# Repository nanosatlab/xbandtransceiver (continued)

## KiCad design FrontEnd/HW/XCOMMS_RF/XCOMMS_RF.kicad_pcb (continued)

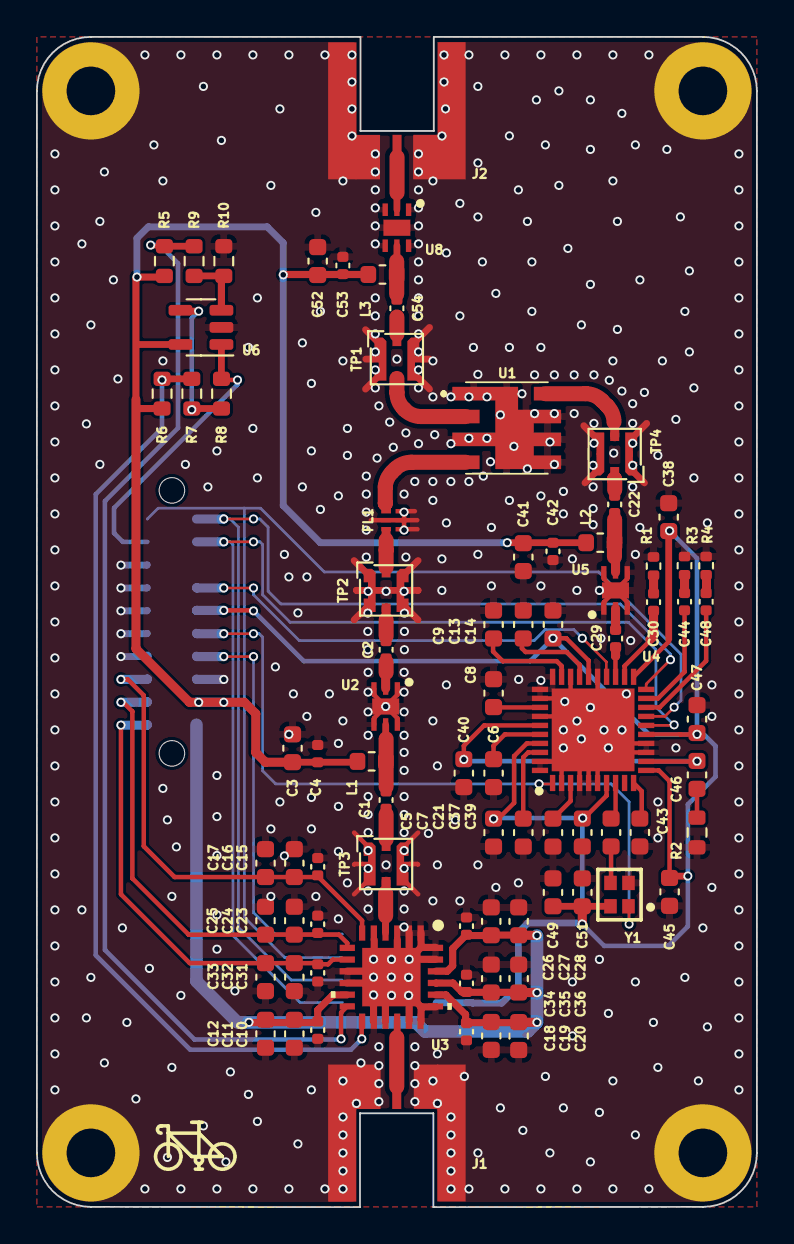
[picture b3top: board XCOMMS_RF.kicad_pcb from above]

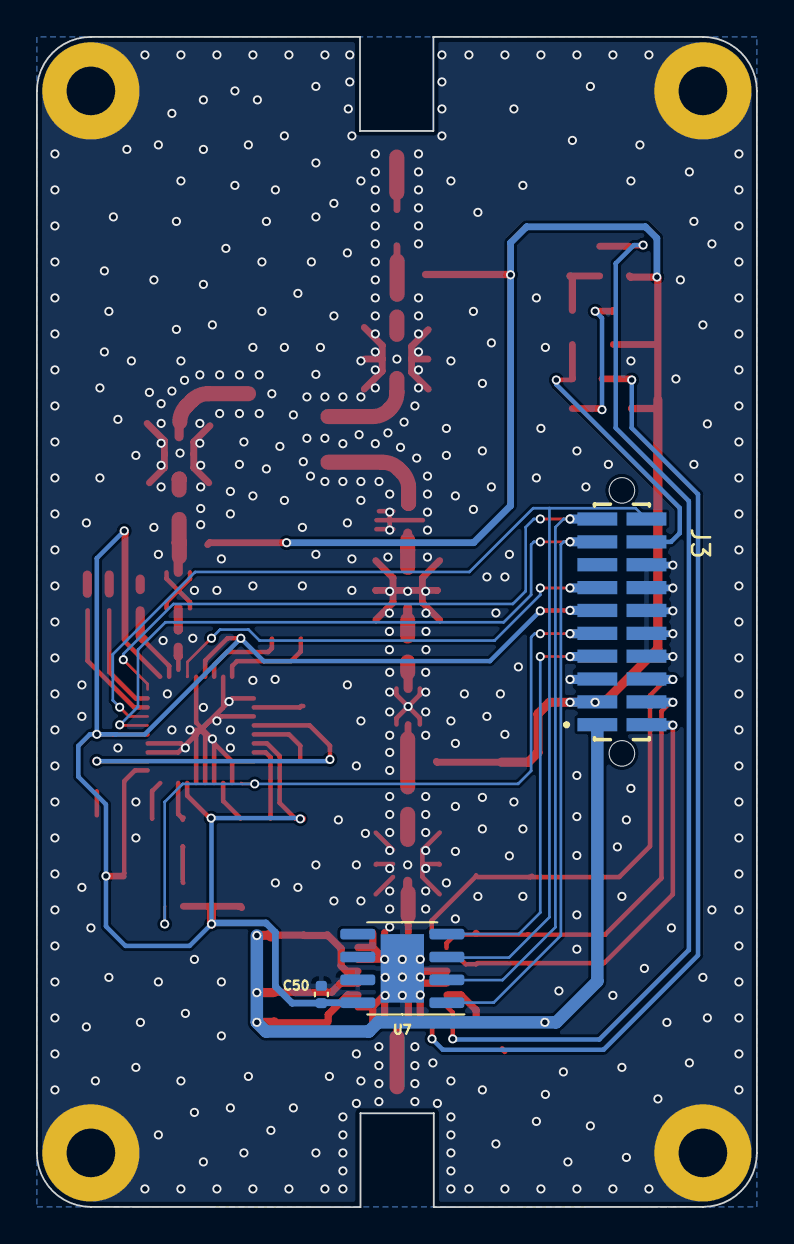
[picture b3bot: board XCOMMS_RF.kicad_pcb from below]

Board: 2 copper layers, 40.0 x 65.0 mm, 88 parts (3 on the bottom side), 52 nets.

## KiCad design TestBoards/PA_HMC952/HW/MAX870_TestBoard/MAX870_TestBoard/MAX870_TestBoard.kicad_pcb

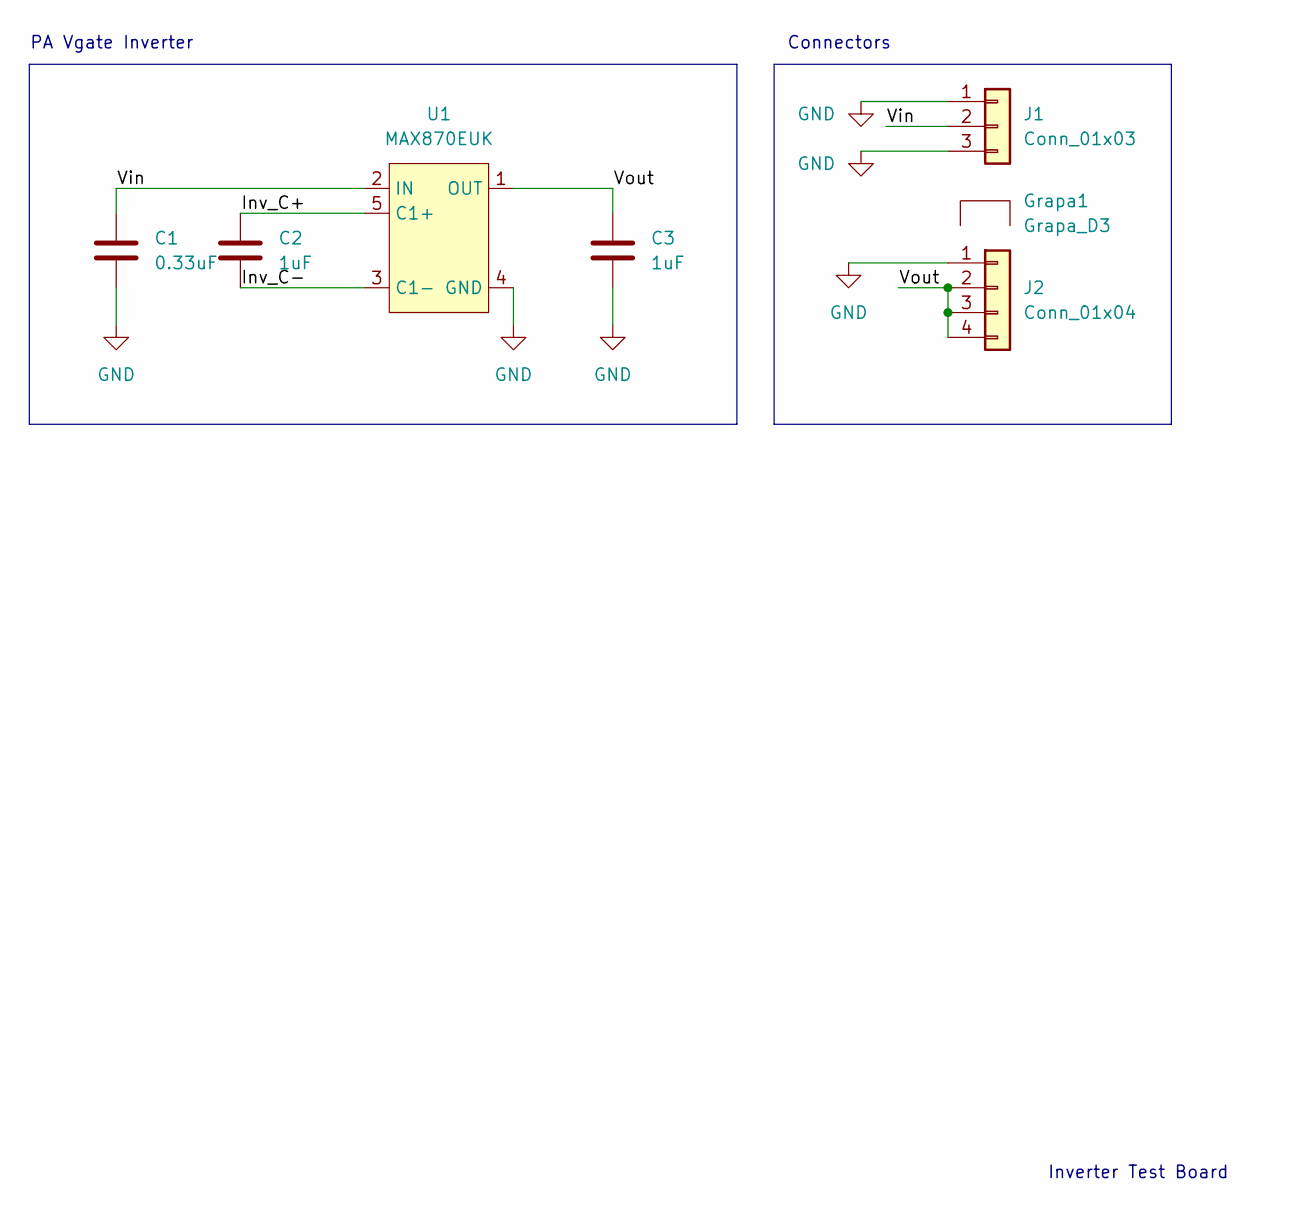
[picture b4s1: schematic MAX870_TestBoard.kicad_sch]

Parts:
C1: 0.33uF; C_0603_1608Metric
C2, C3: 1uF; C_0603_1608Metric
Grapa1: Grapa_D3; Grapa_0.8mm_11.9mm
J1: Conn_01x03; PinHeader_1x03_P2.54mm_Vertical
J2: Conn_01x04; PinHeader_1x04_P2.54mm_Vertical
U1: MAX870EUK; SOT-23-5

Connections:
/Inv_C+: C2.2, U1.5 (C1+)
/Inv_C-: C2.1, U1.3 (C1-)
/Vin: C1.2, J1.2, U1.2 (IN)
/Vout: C3.2, J2.2, J2.3, J2.4, U1.1 (OUT)
GND: C1.1, C3.1, J1.1, J1.3, J2.1, U1.4 (GND)

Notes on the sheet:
PA Vgate Inverter
Connectors
Inverter Test Board

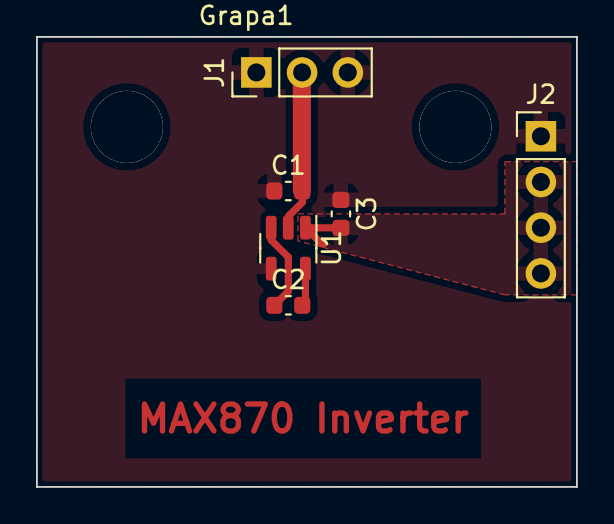
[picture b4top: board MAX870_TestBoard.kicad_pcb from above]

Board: 2 copper layers, 30.0 x 25.0 mm, 7 parts (0 on the bottom side), 5 nets.

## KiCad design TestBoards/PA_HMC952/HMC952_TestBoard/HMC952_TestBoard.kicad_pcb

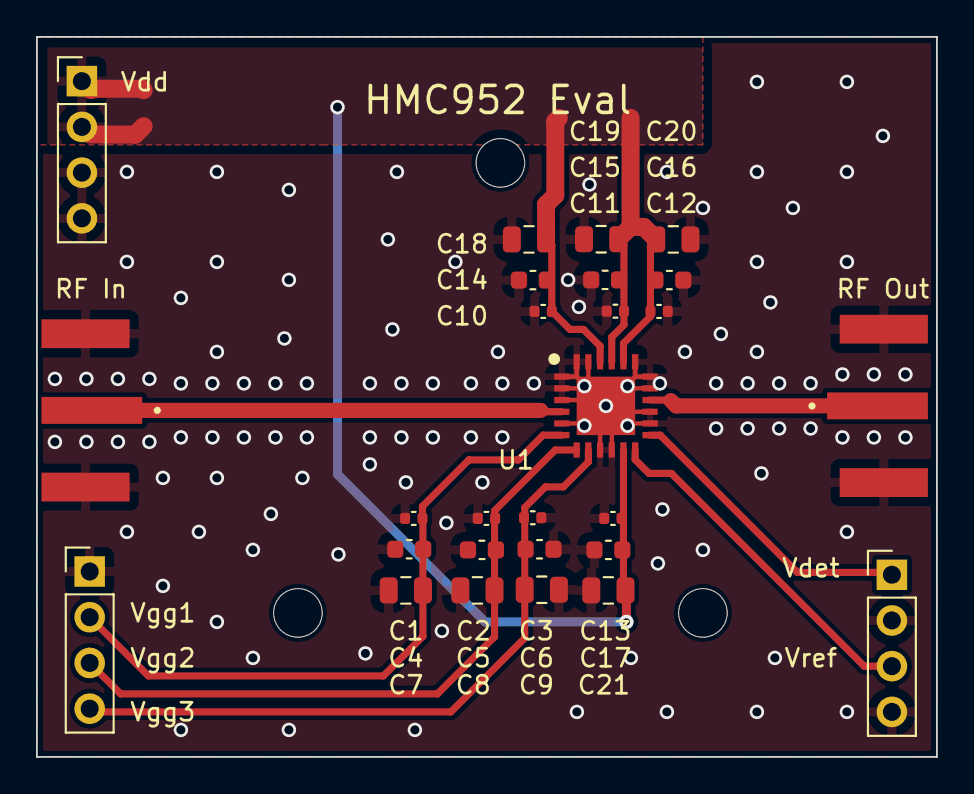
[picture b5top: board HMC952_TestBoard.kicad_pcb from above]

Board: 2 copper layers, 50.0 x 40.0 mm, 30 parts (0 on the bottom side), 9 nets.

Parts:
C1, C2, C3, C10, C11, C12, C13: 100pF; C_0402_1005Metric
C4, C5, C6, C14, C15, C16, C17: 10nF; C_0603_1608Metric
C7, C8, C9, C18, C19, C20, C21: 4.7uF; C_0805_2012Metric
J1, J2: SMA; LINX_CONSMA020.062-G
J3, J4, J5: Conn_01x04; PinHeader_1x04_P2.54mm_Vertical
SCRW1, SCRW2, SCRW3: MountingHole_Pad; MountingHole_2.7mm_M2.5_ISO14580
U1: HMC952ALP5GE; QFN65P500X500X100-25N-D

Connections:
/RF_In: J1.1 (RF), U1.4 (RFIN)
/RF_out: J2.1 (RF), U1.16 (RFOUT)
/Vd_PA: C10.2, C11.2, C12.2, C13.2, C14.2, C15.2, C16.2, C17.2, C18.2, C19.2, C20.2, C21.2, J3.1, J3.2, U1.11 (VDD4), U1.20 (VDD3), U1.21 (VDD2), U1.22 (VDD1)
/Vdet: J5.1, U1.13 (VDET)
/Vg_PA1: C1.2, C4.2, C7.2, J4.2, U1.6 (VGG1)
/Vg_PA2: C2.2, C5.2, C8.2, J4.3, U1.7 (VGG2)
/Vg_PA3: C3.2, C6.2, C9.2, J4.4, U1.8 (VGG3)
/Vref: J5.3, U1.12 (VREF)
GND: C1.1, C2.1, C3.1, C4.1, C5.1, C6.1, C7.1, C8.1, C9.1, C10.1, C11.1, C12.1, C13.1, C14.1, C15.1, C16.1, C17.1, C18.1, C19.1, C20.1, C21.1, J1.S1, J1.S2, J1.S3, J1.S4, J2.S1, J2.S2, J2.S3, J2.S4, J3.3, J3.4, J4.1, J5.2, J5.4, U1.1 (NC_1), U1.2 (NC_2), U1.3 (NC_3), U1.5 (GND_1), U1.9 (NC_4), U1.10 (NC_5), U1.14 (NC_6), U1.15 (GND_2), U1.17 (NC_7), U1.18 (NC_8), U1.19 (NC_9), U1.23 (NC_10), U1.24 (NC_11), U1.25 (THERMAL_PAD)

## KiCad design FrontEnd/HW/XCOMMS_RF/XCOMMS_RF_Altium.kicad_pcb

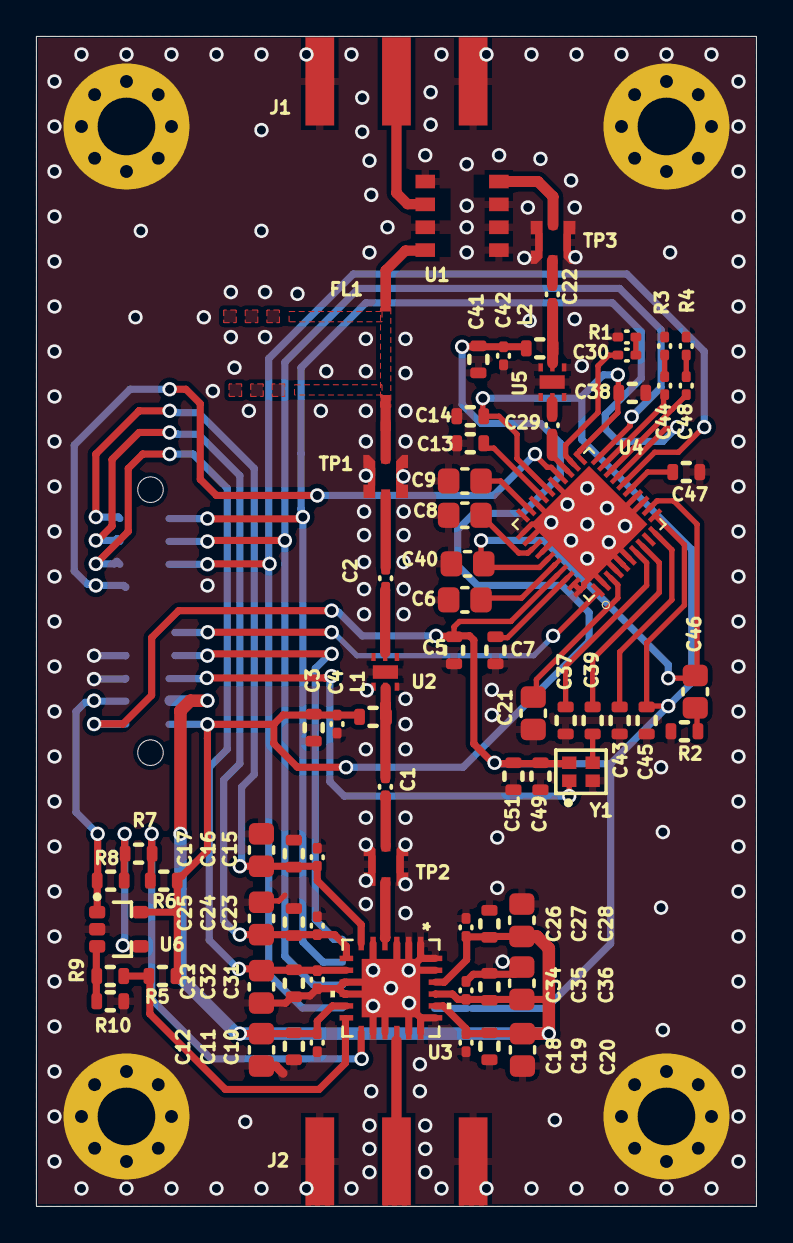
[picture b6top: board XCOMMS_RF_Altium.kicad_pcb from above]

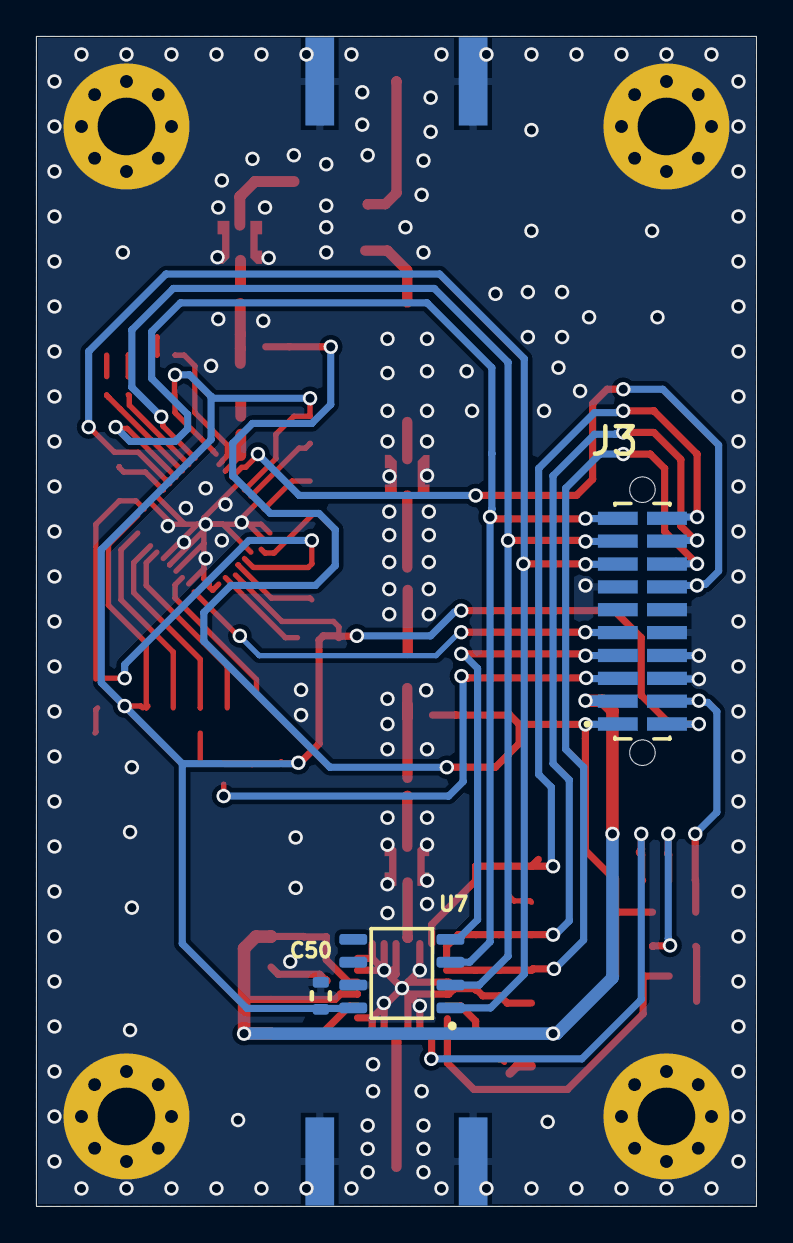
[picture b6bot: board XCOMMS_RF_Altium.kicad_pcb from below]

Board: 2 copper layers, 40.0 x 65.0 mm, 82 parts (3 on the bottom side), 51 nets.

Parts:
C1, C2, C4, C10, C15, C18, C22, C23, C26, C29, C30, C31, C34, C42, C44, C48: Cap Semi; 0402 SND CAPACITOR
C3, C5, C7, C11, C13, C14, C16, C19, C24, C27, C32, C35, C37, C38, C39, C41, C43, C45, C47, C49, C50, C51: Cap Semi; 0603 SMD Capacitor
C6, C8, C9, C12, C17, C20, C21, C25, C28, C33, C36, C40, C46: Cap Semi; 0805 SMD Capacitor
FL1: NotchFilter; Notch_5600to6100MHz
J1, J2: SMA; CONSMA020-062-G
J3: SFC-110-T2-F-D-A-TR; SAMTEC_SFC-110-T2-F-D-A-TR
L1, L2: Inductor; 0603 SMD Inductor
R1, R3, R4: Res3; 0402 SMD Resistor
R2, R5, R6, R7, R8, R9, R10: Res3; 0603 SMD Resistor
SCRW1, SCRW2, SCRW3, SCRW4: Metric Screw Hole; M3 ScrewHole
TP1, TP2, TP3: MSC-156C; MS-156C
U1: SIM-14+; HV1195_Minicircuits
U2, U5: HMC788A
U3: HMC952ALP5GE; CP_24_20_ADI
U4: LMX2572; QFN50P600X600X100-41N
U6: AD8031; SOT-23-5
U7: ADT7310; SOIC-8
Y1: TCXO 25 MHz; ECS-TXO-2016

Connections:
3V3: C5.2, C14.1, C38.1, C45.1, C49.1, C50.2, C51.2, J3.02, U4.11, U4.21, U4.26, U4.37, U7.8, Y1.4
5V: C3.2, C4.2, C41.2, C42.2, J3.01, L1.2, L2.2, R5.2, R6.2, U6.5
GND: C3.1, C4.1, C5.1, C6.2, C7.1, C8.2, C9.1, C10.2, C11.2, C12.2, C13.1, C14.2, C15.2, C16.2, C17.2, C18.2, C19.2, C20.2, C21.1, C23.2, C24.2, C25.2, C26.2, C27.2, C28.2, C31.2, C32.2, C33.2, C34.2, C35.2, C36.2, C37.2, C38.2, C40.1, C41.1, C42.1, C43.1, C45.2, C47.1, C49.2, C50.1, C51.1, J1.2, J1.3, J1.4, J1.5, J2.2, J2.3, J2.4, J2.5, J3.06, J3.08, J3.10, J3.11, J3.12, J3.13, R1.1, R2.2, R3.1, R4.1, R10.2, SCRW1.1, SCRW2.1, SCRW3.1, SCRW4.1, TP1.3, TP1.4, TP2.3, TP2.4, TP3.3, TP3.4, U1.1, U1.3, U1.5, U1.6, U1.7, U2.1, U2.3, U2.4, U2.6, U3.1, U3.2, U3.3, U3.5, U3.9, U3.10, U3.14, U3.15, U3.17, U3.18, U3.19, U3.23, U3.24, U3.25, U4.2, U4.4, U4.5, U4.6, U4.13, U4.14, U4.25, U4.28, U4.30, U4.31, U4.32, U4.34, U4.39, U4.40, U4.41, U5.1, U5.3, U5.4, U5.6, U6.2, U7.7, Y1.2
LO_EN: J3.05, Y1.1
NetC1_1: C1.1, L1.1, U2.5
NetC1_2: C1.2, TP2.1
NetC2_1: C2.1, TP1.2
NetC2_2: C2.2, U2.2
NetC6_1: C6.1, U4.36
NetC7_2: C7.2, U4.38
NetC8_1: C8.1, U4.33
NetC9_2: C9.2, U4.29
NetC13_2: C13.2, U4.27
NetC21_2: C21.2, U4.3
NetC22_1: C22.1, L2.1, U5.5
NetC22_2: C22.2, TP3.1
NetC29_1: C29.1, U4.23
NetC29_2: C29.2, U5.2
NetC30_1: C30.1, U4.22
NetC30_2: C30.2, R1.2
NetC37_1: C37.1, U4.7
NetC39_2: C39.2, U4.8
NetC40_2: C40.2, C46.2, U4.12, U4.35
NetC43_2: C43.2, U4.10
NetC44_1: C44.1, U4.19
NetC44_2: C44.2, R3.2
NetC46_1: C46.1, R2.1
NetC47_2: C47.2, U4.15
NetC48_1: C48.1, R4.2
NetC48_2: C48.2, U4.18
NetFL1_1: FL1.1, TP1.1, U1.4
NetR7_1: R7.1, R8.2, U6.4
NetR9_1: R9.1, R10.1, U6.3
PA_RF_IN: TP2.2, U3.4
PLL_CSB: J3.14, U4.24
PLL_LO: C39.1, Y1.3
RF_Tx_in: J1.1, U1.2
RF_Tx_out: J2.1, U3.16
SCK: J3.15, U4.16, U7.1
SDI: J3.19, U4.17, U7.3
SDO: J3.17, U4.20, U7.2
T_CSB: J3.07, U7.4
Tx_CE: J3.09, U4.1
Tx_LO: TP3.2, U1.8
Tx_PM: J3.04, R8.1, U6.1
Vd_PA: C10.1, C11.1, C12.1, C18.1, C19.1, C20.1, C26.1, C27.1, C28.1, C34.1, C35.1, C36.1, J3.03, U3.11, U3.20, U3.21, U3.22
Vdet: R6.1, R7.2, U3.13
Vg_PA1: C15.1, C16.1, C17.1, J3.20, U3.6
Vg_PA2: C23.1, C24.1, C25.1, J3.18, U3.7
Vg_PA3: C31.1, C32.1, C33.1, J3.16, U3.8
Vref: R5.1, R9.2, U3.12

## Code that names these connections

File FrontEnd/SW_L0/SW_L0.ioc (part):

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Mcu.Name=STM32L053R(6-8)Tx
Mcu.Package=LQFP64
Mcu.UserName=STM32L053R8Tx
PA1.GPIOParameters=GPIO_Label
PA1.GPIO_Label=Pout_PA
PA1.Mode=IN1
PA1.Signal=ADC_IN1
PA13.Mode=Serial_Wire
PA13.Signal=SYS_SWDIO
PA14.Mode=Serial_Wire
PA14.Signal=SYS_SWCLK
PA2.GPIOParameters=GPIO_Label
PA2.GPIO_Label=Id_PA
PA2.Mode=IN2
PA2.Signal=ADC_IN2
PA4.GPIOParameters=GPIO_Label
PA4.GPIO_Label=R_CSB
PA4.Signal=GPIO_Output
PA5.Mode=Full_Duplex_Master
PA5.Signal=SPI1_SCK
PA6.Mode=Full_Duplex_Master
PA6.Signal=SPI1_MISO
PA7.Mode=Full_Duplex_Master
PA7.Signal=SPI1_MOSI
PB0.GPIOParameters=GPIO_Label
PB0.GPIO_Label=EN_6V
PB0.Signal=GPIO_Output
PB1.GPIOParameters=GPIO_Label
PB1.GPIO_Label=EN_5V
PB1.Signal=GPIO_Output
PB3.GPIOParameters=GPIO_Label
PB3.GPIO_Label=T_CSB
PB3.Signal=GPIO_Output
PB4.GPIOParameters=GPIO_Label
PB4.GPIO_Label=Tx_CE
PB4.Signal=GPIO_Output
PB5.GPIOParameters=GPIO_Label
PB5.GPIO_Label=PLL_CSB
PB5.Signal=GPIO_Output
PB6.Mode=I2C
PB6.Signal=I2C1_SCL
PB7.Mode=I2C
PB7.Signal=I2C1_SDA
PH0-OSC_IN.Mode=HSE-External-Clock-Source
PH0-OSC_IN.Signal=RCC_OSC_IN
RCC.HSE_VALUE=8000000
RCC.SYSCLKFreq_VALUE=2097000
board=custom

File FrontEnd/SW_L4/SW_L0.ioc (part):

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Mcu.Name=STM32L431K(B-C)Ux
Mcu.Package=UFQFPN32
Mcu.UserName=STM32L431KBUx
PA0.Mode=HSE-External-Clock-Source-for-LittleOrca
PA0.Signal=RCC_CK_IN
PA1.GPIOParameters=GPIO_Label
PA1.GPIO_Label=Pout_PA
PA1.Signal=ADCx_IN6
PA10.Mode=I2C
PA10.Signal=I2C1_SDA
PA13\ (JTMS-SWDIO).Mode=Serial_Wire
PA13\ (JTMS-SWDIO).Signal=SYS_JTMS-SWDIO
PA14\ (JTCK-SWCLK).Mode=Serial_Wire
PA14\ (JTCK-SWCLK).Signal=SYS_JTCK-SWCLK
PA2.GPIOParameters=GPIO_Label
PA2.GPIO_Label=Id_PA
PA2.Signal=ADCx_IN7
PA4.GPIOParameters=GPIO_Label
PA4.GPIO_Label=R_CSB
PA4.Signal=GPIO_Output
PA5.Mode=Full_Duplex_Master
PA5.Signal=SPI1_SCK
PA6.Mode=Full_Duplex_Master
PA6.Signal=SPI1_MISO
PA7.Mode=Full_Duplex_Master
PA7.Signal=SPI1_MOSI
PA9.Mode=I2C
PA9.Signal=I2C1_SCL
PB0.GPIOParameters=GPIO_Label
PB0.GPIO_Label=EN_6V
PB0.Signal=GPIO_Output
PB1.GPIOParameters=GPIO_Label
PB1.GPIO_Label=EN_5V
PB1.Signal=GPIO_Output
PB3\ (JTDO-TRACESWO).GPIOParameters=GPIO_Label
PB3\ (JTDO-TRACESWO).GPIO_Label=T_CSB
PB3\ (JTDO-TRACESWO).Signal=GPIO_Output
PB4\ (NJTRST).GPIOParameters=GPIO_Label
PB4\ (NJTRST).GPIO_Label=Tx_CE
PB4\ (NJTRST).Signal=GPIO_Output
PB5.GPIOParameters=GPIO_Label
PB5.GPIO_Label=PLL_CSB
PB5.Signal=GPIO_Output
RCC.HSE_VALUE=8000000
board=custom

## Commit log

2021-11-26 added README.md
2021-11-26 added FrontEnd folder
2021-11-26 Added code for programming PLL LMX2572 test baord using registers obtained from TICS PRO software
2021-11-26 added PA test board folder
2021-11-26 added PLL library code
2021-11-26 updated PLL library code
2021-11-26 updated structure
2021-12-02 PLL librray tested, some functions moved from to be tested to working
2021-12-03 worked on lmx2572 lib
2021-12-06 user functions added to LMX2572 library
2021-12-12 LMX2572 library worked
2022-02-05 reorganization
2022-02-05 added subsystem description in README
2022-02-05 started translating altium to kicad
2022-02-05 Altium2Kicad translation
2022-02-16 Altium to KiCad translation of interface board
2022-02-16 Interface board modified
2022-02-21 RF frontend translated to Kicad from Altium
2022-02-21 XCOMMS_RF and XCOMMS_Interface KiCad design updated
2022-02-22 XCOMMS_RF ported to KiCad
2022-02-25 XCOMS_RF updated
2022-03-08 XCOMMS_RF update
2022-03-10 Relaxed Design RUles and output files generated
2022-03-10 HMC592 TB Schematic
2022-03-18 PA TB
2022-03-21 XCOMMS RF update and PA EvalBoard
2022-03-22 XCOMMS RF update
2022-04-07 XCOMMS Interface rebuild
2022-04-07 xtal changed and routing
2022-04-12 redundant MCU
2022-04-12 starting redundant mcu
2022-04-12 continuation of previous
2022-05-02 XCOMMS RF
2022-05-11 simplified PA gate control
2022-05-12 PA code started
2022-05-13 PA gate control updated and Inverter
2022-06-09 don't remember
2022-06-10 shield started
